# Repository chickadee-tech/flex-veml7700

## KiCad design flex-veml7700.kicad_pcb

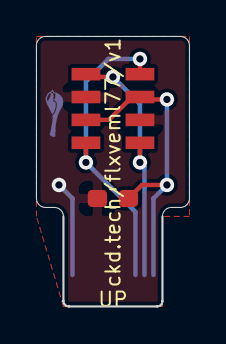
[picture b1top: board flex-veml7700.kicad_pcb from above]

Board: 2 copper layers, 8.5 x 15.0 mm, 4 parts (0 on the bottom side), 4 nets.

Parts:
C1: 0.1uF; C_0603_1608Metric_Pad1.08x0.95mm_HandSolder
J1: 10POSFPC; 10pins-flex
J2, J3: Conn_01x04; VEML7700

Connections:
+3V3: C1.1, J1.10, J2.2, J3.2
/SCL: J1.8, J2.1, J3.1
/SDA: J1.9, J2.4, J3.4
GND: C1.2, J1.1, J2.3, J3.3

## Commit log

2021-02-16 initial version
